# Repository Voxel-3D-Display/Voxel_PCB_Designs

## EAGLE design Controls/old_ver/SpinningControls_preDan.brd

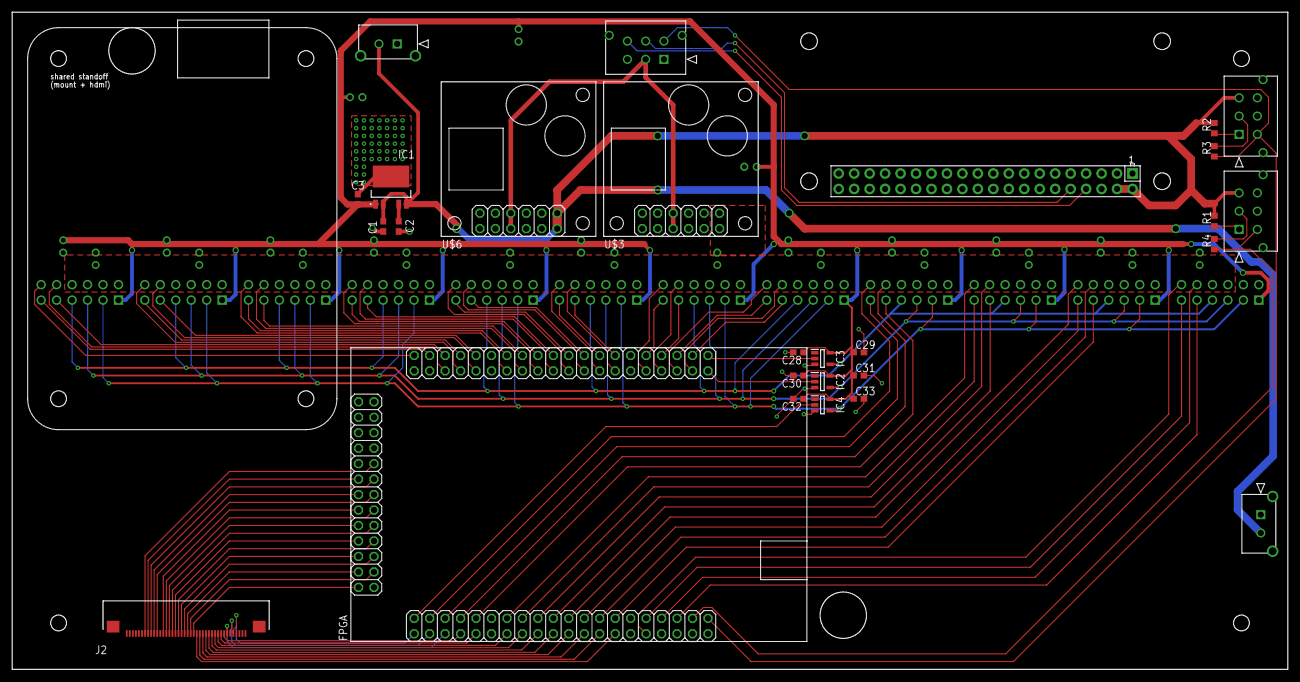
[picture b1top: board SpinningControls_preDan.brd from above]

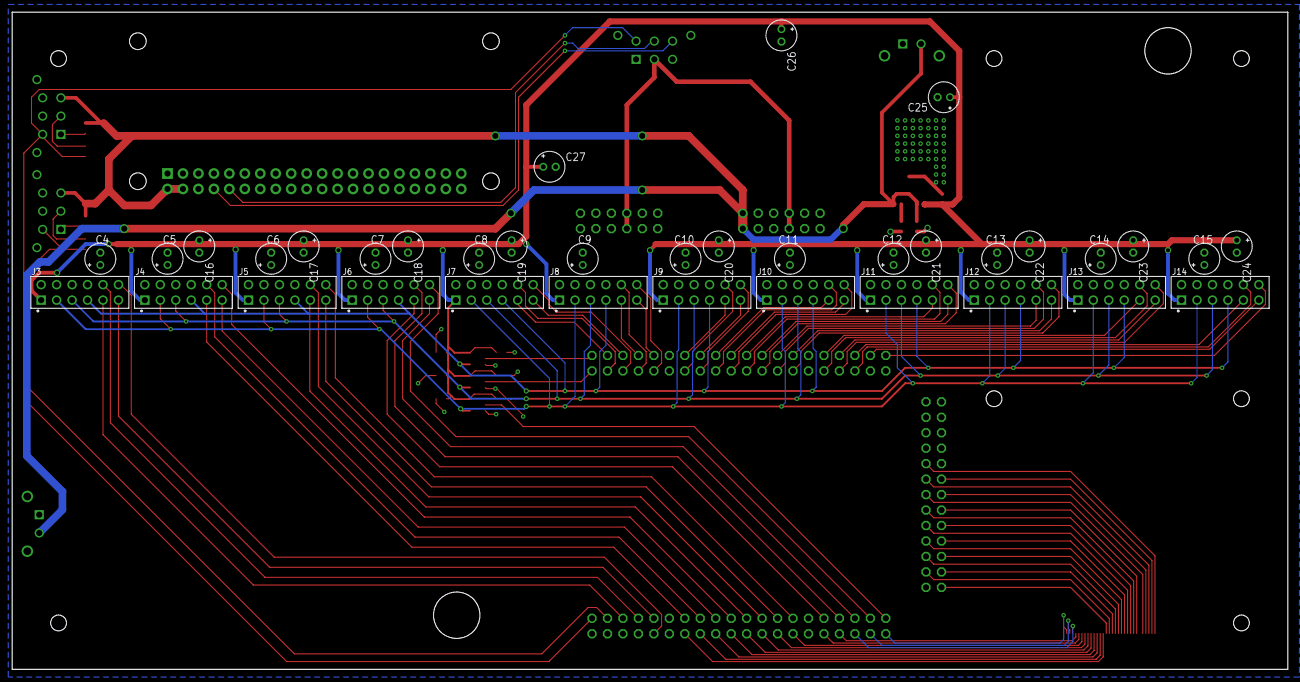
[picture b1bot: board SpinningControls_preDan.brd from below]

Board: 2 copper layers, 209.6 x 107.9 mm, 64 parts (36 on the bottom side), 95 nets.

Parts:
C1, C3: 4.7uF; C0603
C2: 10nF; C0603
C4, C5, C6, C7, C8, C9, C10, C11, C12, C13, C14, C15, C16, C17, C18, C19, C20, C21, C22, C23, C24, C25, C26, C27: 100u; E2-5
C28, C30, C32: 0.1u; C0603
C29, C31, C33: 4.7u; C0603
FPGA: DE0-NANO
IC1: S-19246E33H-V5T2U; S19246E33HV5T2U
IC2, IC3, IC4: SN74LVC1G34DBVR; SOT95P280X145-5N
J2: F32R-1A7H1-11040; F32R1A7H111040
J3, J4, J5, J6, J7, J8, J9, J10, J11, J12, J13, J14: SULLINS_PPPC062LFBN-RCSULLINS_PPPC062LFBN-RC_0_0; SULLINS_PPPC062LFBN-RC_0
J15, J16, J17: 430450612; CON_430450612_MOL
J18, J19: 436500215; CON_436500215_MOL
R1, R2: 165 Ω; R0603
R3, R4: 19.1k Ω; R0603
U$1: RPI-ZERO; RASPBERRYPI_BASTELSTUBE_V13_RASPI_BOARD_B+_FULL
U$2: TFP401
U$3: 3V3_BUCK_REGULATOR; 2X06
U$6: 5V_BUCK_REGULATOR; 2X06

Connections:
3V3_LED: C4.+, C5.+, C6.+, C7.+, C8.+, C9.+, C10.+, C11.+, C12.+, C13.+, C14.+, C15.+, J3.6, J3.8, J4.6, J4.8, J5.6, J5.8, J6.6, J6.8, J7.6, J7.8, J8.6, J8.8, J9.6, J9.8, J10.6, J10.8, J11.6, J11.8, J12.6, J12.8, J13.6, J13.8, J14.6, J14.8, U$3.11, U$3.12
3V3_LOGIC: C3.1, C16.+, C17.+, C18.+, C19.+, C20.+, C21.+, C22.+, C23.+, C24.+, C25.+, C26.+, C27.+, C28.1, C29.1, C30.1, C31.1, C32.1, C33.1, IC1.1, IC2.5, IC3.5, IC4.5, J3.1, J4.1, J5.1, J6.1, J7.1, J8.1, J9.1, J10.1, J11.1, J12.1, J13.1, J14.1
5V: C1.1, IC1.2, IC1.5, J16.3, J17.3, J18.2, J19.2, R1.2, R2.2, U$1.2, U$1.4, U$6.11, U$6.12
24V: J15.2, U$3.5, U$3.6, U$6.5, U$6.6
ACTIVE: FPGA.94, J2.31
B1: FPGA.85, J2.21
B2: FPGA.86, J2.22
B3: FPGA.87, J2.23
B4: FPGA.88, J2.24
B5: FPGA.89, J2.25
B6: FPGA.90, J2.26
B7: FPGA.91, J2.27
B8: FPGA.92, J2.28
DISPEN: FPGA.97, J2.34
ENC_POS: FPGA.41, J15.4, J17.4, R3.1
ENC_POS0: FPGA.43, J16.4, R4.1
G1: FPGA.62, J2.13
G2: FPGA.60, J2.14
G3: FPGA.58, J2.15
G4: FPGA.56, J2.16
G5: FPGA.54, J2.17
G6: FPGA.82, J2.18
G7: FPGA.83, J2.19
G8: FPGA.84, J2.20
GND: C1.2, C2.2, C3.2, C4.-, C5.-, C6.-, C7.-, C8.-, C9.-, C10.-, C11.-, C12.-, C13.-, C14.-, C15.-, C16.-, C17.-, C18.-, C19.-, C20.-, C21.-, C22.-, C23.-, C24.-, C25.-, C26.-, C27.-, C28.2, C29.2, C30.2, C31.2, C32.2, C33.2, IC1.3, IC2.3, IC3.3, IC4.3, J3.2, J3.4, J4.2, J4.4, J5.2, J5.4, J6.2, J6.4, J7.2, J7.4, J8.2, J8.4, J9.2, J9.4, J10.2, J10.4, J11.2, J11.4, J12.2, J12.4, J13.2, J13.4, J14.2, J14.4, J15.1, J15.3, J16.2, J16.5, J17.2, J17.5, J18.1, J19.1, R3.2, R4.2, U$1.6, U$1.9, U$1.14, U$1.20, U$1.25, U$1.30, U$1.34, U$1.39, U$3.7, U$3.8, U$3.9, U$3.10, U$6.7, U$6.8, U$6.9, U$6.10
GSCLK: IC4.4, J3.3, J4.3, J5.3, J6.3, J7.3, J8.3, J9.3, J10.3, J11.3, J12.3, J13.3, J14.3
GSCLK_FPGA: FPGA.79, IC4.2
HSYNC: FPGA.95, J2.32
LAT: IC2.4, J3.5, J4.5, J5.5, J6.5, J7.5, J8.5, J9.5, J10.5, J11.5, J12.5, J13.5, J14.5
LAT_FPGA: FPGA.39, IC2.2
unnamed: J16.1, R1.1
unnamed: C2.1, IC1.4
unnamed: J17.1, R2.1
PIXCLK: FPGA.93, J2.30
PI_RX: J15.5, U$1.10
PI_TX: J15.6, U$1.8
R1: FPGA.80, J2.5
R2: FPGA.78, J2.6
R3: FPGA.76, J2.7
R4: FPGA.74, J2.8
R5: FPGA.72, J2.9
R6: FPGA.68, J2.10
R7: FPGA.66, J2.11
R8: FPGA.64, J2.12
SCLK: IC3.4, J3.7, J4.7, J5.7, J6.7, J7.7, J8.7, J9.7, J10.7, J11.7, J12.7, J13.7, J14.7
SCLK_FPGA: FPGA.40, IC3.2
SIN12_J3: FPGA.50, J3.12
SIN12_J4: FPGA.59, J4.12
SIN12_J5: FPGA.67, J5.12
SIN12_J6: FPGA.77, J6.12
SIN12_J7: FPGA.35, J7.12
SIN12_J8: FPGA.31, J8.12
SIN12_J9: FPGA.25, J9.12
SIN12_J10: FPGA.21, J10.12
SIN12_J11: FPGA.17, J11.12
SIN12_J12: FPGA.13, J12.12
SIN12_J13: FPGA.7, J13.12
SIN12_J14: FPGA.2, J14.12
SIN34_J3: FPGA.49, J3.11
SIN34_J4: FPGA.57, J4.11
SIN34_J5: FPGA.65, J5.11
SIN34_J6: FPGA.75, J6.11
SIN34_J7: FPGA.36, J7.11
SIN34_J8: FPGA.32, J8.11
SIN34_J9: FPGA.26, J9.11
SIN34_J10: FPGA.22, J10.11
SIN34_J11: FPGA.18, J11.11
SIN34_J12: FPGA.14, J12.11
SIN34_J13: FPGA.8, J13.11
SIN34_J14: FPGA.4, J14.11
SIN56_J3: FPGA.47, J3.10
SIN56_J4: FPGA.55, J4.10
SIN56_J5: FPGA.63, J5.10
SIN56_J6: FPGA.73, J6.10
SIN56_J7: FPGA.37, J7.10
SIN56_J8: FPGA.33, J8.10
SIN56_J9: FPGA.27, J9.10
SIN56_J10: FPGA.23, J10.10
SIN56_J11: FPGA.19, J11.10
SIN56_J12: FPGA.15, J12.10
SIN56_J13: FPGA.9, J13.10
SIN56_J14: FPGA.5, J14.10
SIN78_J3: FPGA.45, J3.9
SIN78_J4: FPGA.53, J4.9
SIN78_J5: FPGA.61, J5.9
SIN78_J6: FPGA.71, J6.9
SIN78_J7: FPGA.38, J7.9
SIN78_J8: FPGA.34, J8.9
SIN78_J9: FPGA.28, J9.9
SIN78_J10: FPGA.24, J10.9
SIN78_J11: FPGA.20, J11.9
SIN78_J12: FPGA.16, J12.9
SIN78_J13: FPGA.10, J13.9
SIN78_J14: FPGA.6, J14.9
VSYNC: FPGA.96, J2.33

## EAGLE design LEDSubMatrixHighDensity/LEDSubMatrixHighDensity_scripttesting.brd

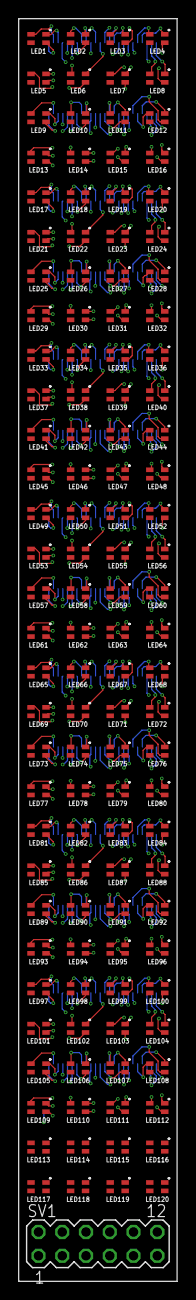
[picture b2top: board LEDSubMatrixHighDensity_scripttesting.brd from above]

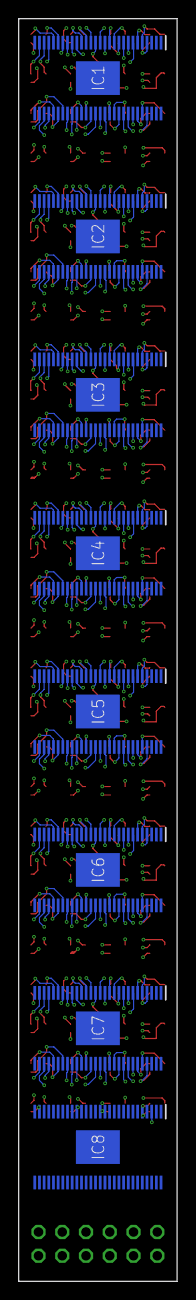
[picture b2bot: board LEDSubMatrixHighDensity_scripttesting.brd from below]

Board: 4 copper layers, 16.9 x 135.0 mm, 129 parts (8 on the bottom side), 369 nets.

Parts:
IC1, IC2, IC3, IC4, IC5, IC6, IC7, IC8: TLC5955DCAR; SOP50P810X120-57N
LED1, LED2, LED3, LED4, LED5, LED6, LED7, LED8, LED9, LED10, LED11, LED12, LED13, LED14, LED15, LED16, LED17, LED18, LED19, LED20, LED21, LED22, LED23, LED24, LED25, LED26, LED27, LED28, LED29, LED30, LED31, LED32, LED33, LED34, LED35, LED36, LED37, LED38, LED39, LED40, LED41, LED42, LED43, LED44, LED45, LED46, LED47, LED48, LED49, LED50, LED51, LED52, LED53, LED54, LED55, LED56, LED57, LED58, LED59, LED60, LED61, LED62, LED63, LED64, LED65, LED66, LED67, LED68, LED69, LED70, LED71, LED72, LED73, LED74, LED75, LED76, LED77, LED78, LED79, LED80, LED81, LED82, LED83, LED84, LED85, LED86, LED87, LED88, LED89, LED90, LED91, LED92, LED93, LED94, LED95, LED96, LED97, LED98, LED99, LED100, LED101, LED102, LED103, LED104, LED105, LED106, LED107, LED108, LED109, LED110, LED111, LED112, LED113, LED114, LED115, LED116, LED117, LED118, LED119, LED120: B38G3RGB
SV1: MA06-2

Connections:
3V3: IC1.54, IC2.54, IC3.54, IC4.54, IC5.54, IC6.54, IC7.54, IC8.54, LED1.3, LED2.3, LED3.3, LED4.3, LED5.3, LED6.3, LED7.3, LED8.3, LED9.3, LED10.3, LED11.3, LED12.3, LED13.3, LED14.3, LED15.3, LED16.3, LED17.3, LED18.3, LED19.3, LED20.3, LED21.3, LED22.3, LED23.3, LED24.3, LED25.3, LED26.3, LED27.3, LED28.3, LED29.3, LED30.3, LED31.3, LED32.3, LED33.3, LED34.3, LED35.3, LED36.3, LED37.3, LED38.3, LED39.3, LED40.3, LED41.3, LED42.3, LED43.3, LED44.3, LED45.3, LED46.3, LED47.3, LED48.3, LED49.3, LED50.3, LED51.3, LED52.3, LED53.3, LED54.3, LED55.3, LED56.3, LED57.3, LED58.3, LED59.3, LED60.3, LED61.3, LED62.3, LED63.3, LED64.3, LED65.3, LED66.3, LED67.3, LED68.3, LED69.3, LED70.3, LED71.3, LED72.3, LED73.3, LED74.3, LED75.3, LED76.3, LED77.3, LED78.3, LED79.3, LED80.3, LED81.3, LED82.3, LED83.3, LED84.3, LED85.3, LED86.3, LED87.3, LED88.3, LED89.3, LED90.3, LED91.3, LED92.3, LED93.3, LED94.3, LED95.3, LED96.3, LED97.3, LED98.3, LED99.3, LED100.3, LED101.3, LED102.3, LED103.3, LED104.3, LED105.3, LED106.3, LED107.3, LED108.3, LED109.3, LED110.3, LED111.3, LED112.3, LED113.3, LED114.3, LED115.3, LED116.3, LED117.3, LED118.3, LED119.3, LED120.3, SV1.3, SV1.9, SV1.10
GND: IC1.29, IC1.56, IC1.57, IC2.29, IC2.56, IC2.57, IC3.29, IC3.56, IC3.57, IC4.29, IC4.56, IC4.57, IC5.29, IC5.56, IC5.57, IC6.29, IC6.56, IC6.57, IC7.29, IC7.56, IC7.57, IC8.29, IC8.56, IC8.57, SV1.1, SV1.11, SV1.12
GSCLK: IC1.55, IC2.55, IC3.55, IC4.55, IC5.55, IC6.55, IC7.55, IC8.55, SV1.6
LAT: IC1.3, IC2.3, IC3.3, IC4.3, IC5.3, IC6.3, IC7.3, IC8.3, SV1.4, SV1.8
N$LEDB1_IC1_PIN4: IC1.4, LED1.2
N$LEDB2_IC1_PIN10: IC1.10, LED2.2
N$LEDB3_IC1_PIN16: IC1.16, LED3.2
N$LEDB4_IC1_PIN22: IC1.22, LED4.2
N$LEDB5_IC1_PIN7: IC1.7, LED5.2
N$LEDB6_IC1_PIN13: IC1.13, LED6.2
N$LEDB7_IC1_PIN19: IC1.19, LED7.2
N$LEDB8_IC1_PIN25: IC1.25, LED8.2
N$LEDB9_IC1_PIN53: IC1.53, LED9.2
N$LEDB10_IC1_PIN47: IC1.47, LED10.2
N$LEDB11_IC1_PIN41: IC1.41, LED11.2
N$LEDB12_IC1_PIN35: IC1.35, LED12.2
N$LEDB13_IC1_PIN50: IC1.50, LED13.2
N$LEDB14_IC1_PIN44: IC1.44, LED14.2
N$LEDB15_IC1_PIN38: IC1.38, LED15.2
N$LEDB16_IC1_PIN32: IC1.32, LED16.2
N$LEDB17_IC2_PIN4: IC2.4, LED17.2
N$LEDB18_IC2_PIN10: IC2.10, LED18.2
N$LEDB19_IC2_PIN16: IC2.16, LED19.2
N$LEDB20_IC2_PIN22: IC2.22, LED20.2
N$LEDB21_IC2_PIN7: IC2.7, LED21.2
N$LEDB22_IC2_PIN13: IC2.13, LED22.2
N$LEDB23_IC2_PIN19: IC2.19, LED23.2
N$LEDB24_IC2_PIN25: IC2.25, LED24.2
N$LEDB25_IC2_PIN53: IC2.53, LED25.2
N$LEDB26_IC2_PIN47: IC2.47, LED26.2
N$LEDB27_IC2_PIN41: IC2.41, LED27.2
N$LEDB28_IC2_PIN35: IC2.35, LED28.2
N$LEDB29_IC2_PIN50: IC2.50, LED29.2
N$LEDB30_IC2_PIN44: IC2.44, LED30.2
N$LEDB31_IC2_PIN38: IC2.38, LED31.2
N$LEDB32_IC2_PIN32: IC2.32, LED32.2
N$LEDB33_IC3_PIN4: IC3.4, LED33.2
N$LEDB34_IC3_PIN10: IC3.10, LED34.2
N$LEDB35_IC3_PIN16: IC3.16, LED35.2
N$LEDB36_IC3_PIN22: IC3.22, LED36.2
N$LEDB37_IC3_PIN7: IC3.7, LED37.2
N$LEDB38_IC3_PIN13: IC3.13, LED38.2
N$LEDB39_IC3_PIN19: IC3.19, LED39.2
N$LEDB40_IC3_PIN25: IC3.25, LED40.2
N$LEDB41_IC3_PIN53: IC3.53, LED41.2
N$LEDB42_IC3_PIN47: IC3.47, LED42.2
N$LEDB43_IC3_PIN41: IC3.41, LED43.2
N$LEDB44_IC3_PIN35: IC3.35, LED44.2
N$LEDB45_IC3_PIN50: IC3.50, LED45.2
N$LEDB46_IC3_PIN44: IC3.44, LED46.2
N$LEDB47_IC3_PIN38: IC3.38, LED47.2
N$LEDB48_IC3_PIN32: IC3.32, LED48.2
N$LEDB49_IC4_PIN4: IC4.4, LED49.2
N$LEDB50_IC4_PIN10: IC4.10, LED50.2
N$LEDB51_IC4_PIN16: IC4.16, LED51.2
N$LEDB52_IC4_PIN22: IC4.22, LED52.2
N$LEDB53_IC4_PIN7: IC4.7, LED53.2
N$LEDB54_IC4_PIN13: IC4.13, LED54.2
N$LEDB55_IC4_PIN19: IC4.19, LED55.2
N$LEDB56_IC4_PIN25: IC4.25, LED56.2
N$LEDB57_IC4_PIN53: IC4.53, LED57.2
N$LEDB58_IC4_PIN47: IC4.47, LED58.2
N$LEDB59_IC4_PIN41: IC4.41, LED59.2
N$LEDB60_IC4_PIN35: IC4.35, LED60.2
N$LEDB61_IC4_PIN50: IC4.50, LED61.2
N$LEDB62_IC4_PIN44: IC4.44, LED62.2
N$LEDB63_IC4_PIN38: IC4.38, LED63.2
N$LEDB64_IC4_PIN32: IC4.32, LED64.2
N$LEDB65_IC5_PIN4: IC5.4, LED65.2
N$LEDB66_IC5_PIN10: IC5.10, LED66.2
N$LEDB67_IC5_PIN16: IC5.16, LED67.2
N$LEDB68_IC5_PIN22: IC5.22, LED68.2
N$LEDB69_IC5_PIN7: IC5.7, LED69.2
N$LEDB70_IC5_PIN13: IC5.13, LED70.2
N$LEDB71_IC5_PIN19: IC5.19, LED71.2
N$LEDB72_IC5_PIN25: IC5.25, LED72.2
N$LEDB73_IC5_PIN53: IC5.53, LED73.2
N$LEDB74_IC5_PIN47: IC5.47, LED74.2
N$LEDB75_IC5_PIN41: IC5.41, LED75.2
N$LEDB76_IC5_PIN35: IC5.35, LED76.2
N$LEDB77_IC5_PIN50: IC5.50, LED77.2
N$LEDB78_IC5_PIN44: IC5.44, LED78.2
N$LEDB79_IC5_PIN38: IC5.38, LED79.2
N$LEDB80_IC5_PIN32: IC5.32, LED80.2
N$LEDB81_IC6_PIN4: IC6.4, LED81.2
N$LEDB82_IC6_PIN10: IC6.10, LED82.2
N$LEDB83_IC6_PIN16: IC6.16, LED83.2
N$LEDB84_IC6_PIN22: IC6.22, LED84.2
N$LEDB85_IC6_PIN7: IC6.7, LED85.2
N$LEDB86_IC6_PIN13: IC6.13, LED86.2
N$LEDB87_IC6_PIN19: IC6.19, LED87.2
N$LEDB88_IC6_PIN25: IC6.25, LED88.2
N$LEDB89_IC6_PIN53: IC6.53, LED89.2
N$LEDB90_IC6_PIN47: IC6.47, LED90.2
N$LEDB91_IC6_PIN41: IC6.41, LED91.2
N$LEDB92_IC6_PIN35: IC6.35, LED92.2
N$LEDB93_IC6_PIN50: IC6.50, LED93.2
N$LEDB94_IC6_PIN44: IC6.44, LED94.2
N$LEDB95_IC6_PIN38: IC6.38, LED95.2
N$LEDB96_IC6_PIN32: IC6.32, LED96.2
N$LEDB97_IC7_PIN4: IC7.4, LED97.2
N$LEDB98_IC7_PIN10: IC7.10, LED98.2
N$LEDB99_IC7_PIN16: IC7.16, LED99.2
N$LEDB100_IC7_PIN22: IC7.22, LED100.2
N$LEDB101_IC7_PIN7: IC7.7, LED101.2
N$LEDB102_IC7_PIN13: IC7.13, LED102.2
N$LEDB103_IC7_PIN19: IC7.19, LED103.2
N$LEDB104_IC7_PIN25: IC7.25, LED104.2
N$LEDB105_IC7_PIN53: IC7.53, LED105.2
N$LEDB106_IC7_PIN47: IC7.47, LED106.2
N$LEDB107_IC7_PIN41: IC7.41, LED107.2
N$LEDB108_IC7_PIN35: IC7.35, LED108.2
N$LEDB109_IC7_PIN50: IC7.50, LED109.2
N$LEDB110_IC7_PIN44: IC7.44, LED110.2
N$LEDB111_IC7_PIN38: IC7.38, LED111.2
N$LEDB112_IC7_PIN32: IC7.32, LED112.2
N$LEDB113_IC8_PIN4: IC8.4, LED113.2
N$LEDB114_IC8_PIN10: IC8.10, LED114.2
N$LEDB115_IC8_PIN16: IC8.16, LED115.2
N$LEDB116_IC8_PIN22: IC8.22, LED116.2
N$LEDB117_IC8_PIN7: IC8.7, LED117.2
N$LEDB118_IC8_PIN13: IC8.13, LED118.2
N$LEDB119_IC8_PIN19: IC8.19, LED119.2
N$LEDB120_IC8_PIN25: IC8.25, LED120.2
N$LEDG1_IC1_PIN6: IC1.6, LED1.1
N$LEDG2_IC1_PIN12: IC1.12, LED2.1
N$LEDG3_IC1_PIN18: IC1.18, LED3.1
N$LEDG4_IC1_PIN24: IC1.24, LED4.1
N$LEDG5_IC1_PIN9: IC1.9, LED5.1
N$LEDG6_IC1_PIN15: IC1.15, LED6.1
N$LEDG7_IC1_PIN21: IC1.21, LED7.1
N$LEDG8_IC1_PIN27: IC1.27, LED8.1
N$LEDG9_IC1_PIN51: IC1.51, LED9.1
N$LEDG10_IC1_PIN45: IC1.45, LED10.1
N$LEDG11_IC1_PIN39: IC1.39, LED11.1
N$LEDG12_IC1_PIN33: IC1.33, LED12.1
N$LEDG13_IC1_PIN48: IC1.48, LED13.1
N$LEDG14_IC1_PIN42: IC1.42, LED14.1
N$LEDG15_IC1_PIN36: IC1.36, LED15.1
N$LEDG16_IC1_PIN30: IC1.30, LED16.1
N$LEDG17_IC2_PIN6: IC2.6, LED17.1
N$LEDG18_IC2_PIN12: IC2.12, LED18.1
N$LEDG19_IC2_PIN18: IC2.18, LED19.1
N$LEDG20_IC2_PIN24: IC2.24, LED20.1
N$LEDG21_IC2_PIN9: IC2.9, LED21.1
N$LEDG22_IC2_PIN15: IC2.15, LED22.1
N$LEDG23_IC2_PIN21: IC2.21, LED23.1
N$LEDG24_IC2_PIN27: IC2.27, LED24.1
N$LEDG25_IC2_PIN51: IC2.51, LED25.1
N$LEDG26_IC2_PIN45: IC2.45, LED26.1
N$LEDG27_IC2_PIN39: IC2.39, LED27.1
N$LEDG28_IC2_PIN33: IC2.33, LED28.1
N$LEDG29_IC2_PIN48: IC2.48, LED29.1
N$LEDG30_IC2_PIN42: IC2.42, LED30.1
N$LEDG31_IC2_PIN36: IC2.36, LED31.1
N$LEDG32_IC2_PIN30: IC2.30, LED32.1
N$LEDG33_IC3_PIN6: IC3.6, LED33.1
N$LEDG34_IC3_PIN12: IC3.12, LED34.1
N$LEDG35_IC3_PIN18: IC3.18, LED35.1
N$LEDG36_IC3_PIN24: IC3.24, LED36.1
N$LEDG37_IC3_PIN9: IC3.9, LED37.1
N$LEDG38_IC3_PIN15: IC3.15, LED38.1
N$LEDG39_IC3_PIN21: IC3.21, LED39.1
N$LEDG40_IC3_PIN27: IC3.27, LED40.1
N$LEDG41_IC3_PIN51: IC3.51, LED41.1
N$LEDG42_IC3_PIN45: IC3.45, LED42.1
N$LEDG43_IC3_PIN39: IC3.39, LED43.1
N$LEDG44_IC3_PIN33: IC3.33, LED44.1
N$LEDG45_IC3_PIN48: IC3.48, LED45.1
N$LEDG46_IC3_PIN42: IC3.42, LED46.1
N$LEDG47_IC3_PIN36: IC3.36, LED47.1
N$LEDG48_IC3_PIN30: IC3.30, LED48.1
N$LEDG49_IC4_PIN6: IC4.6, LED49.1
N$LEDG50_IC4_PIN12: IC4.12, LED50.1
N$LEDG51_IC4_PIN18: IC4.18, LED51.1
N$LEDG52_IC4_PIN24: IC4.24, LED52.1
N$LEDG53_IC4_PIN9: IC4.9, LED53.1
N$LEDG54_IC4_PIN15: IC4.15, LED54.1
N$LEDG55_IC4_PIN21: IC4.21, LED55.1
N$LEDG56_IC4_PIN27: IC4.27, LED56.1
N$LEDG57_IC4_PIN51: IC4.51, LED57.1
N$LEDG58_IC4_PIN45: IC4.45, LED58.1
N$LEDG59_IC4_PIN39: IC4.39, LED59.1
N$LEDG60_IC4_PIN33: IC4.33, LED60.1
N$LEDG61_IC4_PIN48: IC4.48, LED61.1
N$LEDG62_IC4_PIN42: IC4.42, LED62.1
N$LEDG63_IC4_PIN36: IC4.36, LED63.1
N$LEDG64_IC4_PIN30: IC4.30, LED64.1
N$LEDG65_IC5_PIN6: IC5.6, LED65.1
N$LEDG66_IC5_PIN12: IC5.12, LED66.1
N$LEDG67_IC5_PIN18: IC5.18, LED67.1
N$LEDG68_IC5_PIN24: IC5.24, LED68.1
N$LEDG69_IC5_PIN9: IC5.9, LED69.1
N$LEDG70_IC5_PIN15: IC5.15, LED70.1
N$LEDG71_IC5_PIN21: IC5.21, LED71.1
N$LEDG72_IC5_PIN27: IC5.27, LED72.1
N$LEDG73_IC5_PIN51: IC5.51, LED73.1
N$LEDG74_IC5_PIN45: IC5.45, LED74.1
N$LEDG75_IC5_PIN39: IC5.39, LED75.1
N$LEDG76_IC5_PIN33: IC5.33, LED76.1
N$LEDG77_IC5_PIN48: IC5.48, LED77.1
N$LEDG78_IC5_PIN42: IC5.42, LED78.1
N$LEDG79_IC5_PIN36: IC5.36, LED79.1
N$LEDG80_IC5_PIN30: IC5.30, LED80.1
N$LEDG81_IC6_PIN6: IC6.6, LED81.1
N$LEDG82_IC6_PIN12: IC6.12, LED82.1
N$LEDG83_IC6_PIN18: IC6.18, LED83.1
N$LEDG84_IC6_PIN24: IC6.24, LED84.1
N$LEDG85_IC6_PIN9: IC6.9, LED85.1
N$LEDG86_IC6_PIN15: IC6.15, LED86.1
N$LEDG87_IC6_PIN21: IC6.21, LED87.1
N$LEDG88_IC6_PIN27: IC6.27, LED88.1
N$LEDG89_IC6_PIN51: IC6.51, LED89.1
N$LEDG90_IC6_PIN45: IC6.45, LED90.1
N$LEDG91_IC6_PIN39: IC6.39, LED91.1
N$LEDG92_IC6_PIN33: IC6.33, LED92.1
N$LEDG93_IC6_PIN48: IC6.48, LED93.1
N$LEDG94_IC6_PIN42: IC6.42, LED94.1
N$LEDG95_IC6_PIN36: IC6.36, LED95.1
N$LEDG96_IC6_PIN30: IC6.30, LED96.1
N$LEDG97_IC7_PIN6: IC7.6, LED97.1
N$LEDG98_IC7_PIN12: IC7.12, LED98.1
N$LEDG99_IC7_PIN18: IC7.18, LED99.1
N$LEDG100_IC7_PIN24: IC7.24, LED100.1
N$LEDG101_IC7_PIN9: IC7.9, LED101.1
N$LEDG102_IC7_PIN15: IC7.15, LED102.1
N$LEDG103_IC7_PIN21: IC7.21, LED103.1
N$LEDG104_IC7_PIN27: IC7.27, LED104.1
N$LEDG105_IC7_PIN51: IC7.51, LED105.1
N$LEDG106_IC7_PIN45: IC7.45, LED106.1
N$LEDG107_IC7_PIN39: IC7.39, LED107.1
N$LEDG108_IC7_PIN33: IC7.33, LED108.1
N$LEDG109_IC7_PIN48: IC7.48, LED109.1
N$LEDG110_IC7_PIN42: IC7.42, LED110.1
N$LEDG111_IC7_PIN36: IC7.36, LED111.1
N$LEDG112_IC7_PIN30: IC7.30, LED112.1
N$LEDG113_IC8_PIN6: IC8.6, LED113.1
N$LEDG114_IC8_PIN12: IC8.12, LED114.1
N$LEDG115_IC8_PIN18: IC8.18, LED115.1
N$LEDG116_IC8_PIN24: IC8.24, LED116.1
N$LEDG117_IC8_PIN9: IC8.9, LED117.1
N$LEDG118_IC8_PIN15: IC8.15, LED118.1
N$LEDG119_IC8_PIN21: IC8.21, LED119.1
N$LEDG120_IC8_PIN27: IC8.27, LED120.1
N$LEDR1_IC1_PIN5: IC1.5, LED1.4
N$LEDR2_IC1_PIN11: IC1.11, LED2.4
N$LEDR3_IC1_PIN17: IC1.17, LED3.4
N$LEDR4_IC1_PIN23: IC1.23, LED4.4
N$LEDR5_IC1_PIN8: IC1.8, LED5.4
N$LEDR6_IC1_PIN14: IC1.14, LED6.4
N$LEDR7_IC1_PIN20: IC1.20, LED7.4
N$LEDR8_IC1_PIN26: IC1.26, LED8.4
N$LEDR9_IC1_PIN52: IC1.52, LED9.4
N$LEDR10_IC1_PIN46: IC1.46, LED10.4
N$LEDR11_IC1_PIN40: IC1.40, LED11.4
N$LEDR12_IC1_PIN34: IC1.34, LED12.4
N$LEDR13_IC1_PIN49: IC1.49, LED13.4
N$LEDR14_IC1_PIN43: IC1.43, LED14.4
N$LEDR15_IC1_PIN37: IC1.37, LED15.4
N$LEDR16_IC1_PIN31: IC1.31, LED16.4
N$LEDR17_IC2_PIN5: IC2.5, LED17.4
N$LEDR18_IC2_PIN11: IC2.11, LED18.4
N$LEDR19_IC2_PIN17: IC2.17, LED19.4
N$LEDR20_IC2_PIN23: IC2.23, LED20.4
N$LEDR21_IC2_PIN8: IC2.8, LED21.4
N$LEDR22_IC2_PIN14: IC2.14, LED22.4
N$LEDR23_IC2_PIN20: IC2.20, LED23.4
N$LEDR24_IC2_PIN26: IC2.26, LED24.4
N$LEDR25_IC2_PIN52: IC2.52, LED25.4
N$LEDR26_IC2_PIN46: IC2.46, LED26.4
N$LEDR27_IC2_PIN40: IC2.40, LED27.4
N$LEDR28_IC2_PIN34: IC2.34, LED28.4
N$LEDR29_IC2_PIN49: IC2.49, LED29.4
N$LEDR30_IC2_PIN43: IC2.43, LED30.4
N$LEDR31_IC2_PIN37: IC2.37, LED31.4
N$LEDR32_IC2_PIN31: IC2.31, LED32.4
N$LEDR33_IC3_PIN5: IC3.5, LED33.4
N$LEDR34_IC3_PIN11: IC3.11, LED34.4
N$LEDR35_IC3_PIN17: IC3.17, LED35.4
N$LEDR36_IC3_PIN23: IC3.23, LED36.4
N$LEDR37_IC3_PIN8: IC3.8, LED37.4
N$LEDR38_IC3_PIN14: IC3.14, LED38.4
N$LEDR39_IC3_PIN20: IC3.20, LED39.4
N$LEDR40_IC3_PIN26: IC3.26, LED40.4
N$LEDR41_IC3_PIN52: IC3.52, LED41.4
N$LEDR42_IC3_PIN46: IC3.46, LED42.4
N$LEDR43_IC3_PIN40: IC3.40, LED43.4
N$LEDR44_IC3_PIN34: IC3.34, LED44.4
N$LEDR45_IC3_PIN49: IC3.49, LED45.4
N$LEDR46_IC3_PIN43: IC3.43, LED46.4
N$LEDR47_IC3_PIN37: IC3.37, LED47.4
N$LEDR48_IC3_PIN31: IC3.31, LED48.4
N$LEDR49_IC4_PIN5: IC4.5, LED49.4
N$LEDR50_IC4_PIN11: IC4.11, LED50.4
N$LEDR51_IC4_PIN17: IC4.17, LED51.4
N$LEDR52_IC4_PIN23: IC4.23, LED52.4
N$LEDR53_IC4_PIN8: IC4.8, LED53.4
N$LEDR54_IC4_PIN14: IC4.14, LED54.4
N$LEDR55_IC4_PIN20: IC4.20, LED55.4
N$LEDR56_IC4_PIN26: IC4.26, LED56.4
N$LEDR57_IC4_PIN52: IC4.52, LED57.4
N$LEDR58_IC4_PIN46: IC4.46, LED58.4
N$LEDR59_IC4_PIN40: IC4.40, LED59.4
N$LEDR60_IC4_PIN34: IC4.34, LED60.4
N$LEDR61_IC4_PIN49: IC4.49, LED61.4
N$LEDR62_IC4_PIN43: IC4.43, LED62.4
N$LEDR63_IC4_PIN37: IC4.37, LED63.4
N$LEDR64_IC4_PIN31: IC4.31, LED64.4
N$LEDR65_IC5_PIN5: IC5.5, LED65.4
N$LEDR66_IC5_PIN11: IC5.11, LED66.4
N$LEDR67_IC5_PIN17: IC5.17, LED67.4
N$LEDR68_IC5_PIN23: IC5.23, LED68.4
N$LEDR69_IC5_PIN8: IC5.8, LED69.4
N$LEDR70_IC5_PIN14: IC5.14, LED70.4
N$LEDR71_IC5_PIN20: IC5.20, LED71.4
N$LEDR72_IC5_PIN26: IC5.26, LED72.4
N$LEDR73_IC5_PIN52: IC5.52, LED73.4
N$LEDR74_IC5_PIN46: IC5.46, LED74.4
N$LEDR75_IC5_PIN40: IC5.40, LED75.4
N$LEDR76_IC5_PIN34: IC5.34, LED76.4
N$LEDR77_IC5_PIN49: IC5.49, LED77.4
N$LEDR78_IC5_PIN43: IC5.43, LED78.4
N$LEDR79_IC5_PIN37: IC5.37, LED79.4
N$LEDR80_IC5_PIN31: IC5.31, LED80.4
N$LEDR81_IC6_PIN5: IC6.5, LED81.4
N$LEDR82_IC6_PIN11: IC6.11, LED82.4
N$LEDR83_IC6_PIN17: IC6.17, LED83.4
N$LEDR84_IC6_PIN23: IC6.23, LED84.4
N$LEDR85_IC6_PIN8: IC6.8, LED85.4
N$LEDR86_IC6_PIN14: IC6.14, LED86.4
N$LEDR87_IC6_PIN20: IC6.20, LED87.4
N$LEDR88_IC6_PIN26: IC6.26, LED88.4
N$LEDR89_IC6_PIN52: IC6.52, LED89.4
N$LEDR90_IC6_PIN46: IC6.46, LED90.4
N$LEDR91_IC6_PIN40: IC6.40, LED91.4
N$LEDR92_IC6_PIN34: IC6.34, LED92.4
N$LEDR93_IC6_PIN49: IC6.49, LED93.4
N$LEDR94_IC6_PIN43: IC6.43, LED94.4
N$LEDR95_IC6_PIN37: IC6.37, LED95.4
N$LEDR96_IC6_PIN31: IC6.31, LED96.4
N$LEDR97_IC7_PIN5: IC7.5, LED97.4
N$LEDR98_IC7_PIN11: IC7.11, LED98.4
N$LEDR99_IC7_PIN17: IC7.17, LED99.4
N$LEDR100_IC7_PIN23: IC7.23, LED100.4
N$LEDR101_IC7_PIN8: IC7.8, LED101.4
N$LEDR102_IC7_PIN14: IC7.14, LED102.4
N$LEDR103_IC7_PIN20: IC7.20, LED103.4
N$LEDR104_IC7_PIN26: IC7.26, LED104.4
N$LEDR105_IC7_PIN52: IC7.52, LED105.4
N$LEDR106_IC7_PIN46: IC7.46, LED106.4
N$LEDR107_IC7_PIN40: IC7.40, LED107.4
N$LEDR108_IC7_PIN34: IC7.34, LED108.4
N$LEDR109_IC7_PIN49: IC7.49, LED109.4
N$LEDR110_IC7_PIN43: IC7.43, LED110.4
N$LEDR111_IC7_PIN37: IC7.37, LED111.4
N$LEDR112_IC7_PIN31: IC7.31, LED112.4
N$LEDR113_IC8_PIN5: IC8.5, LED113.4
N$LEDR114_IC8_PIN11: IC8.11, LED114.4
N$LEDR115_IC8_PIN17: IC8.17, LED115.4
N$LEDR116_IC8_PIN23: IC8.23, LED116.4
N$LEDR117_IC8_PIN8: IC8.8, LED117.4
N$LEDR118_IC8_PIN14: IC8.14, LED118.4
N$LEDR119_IC8_PIN20: IC8.20, LED119.4
N$LEDR120_IC8_PIN26: IC8.26, LED120.4
SCLK: IC1.2, IC2.2, IC3.2, IC4.2, IC5.2, IC6.2, IC7.2, IC8.2, SV1.2, SV1.7
SIN_1,2: IC1.1, IC2.1
SIN_3,4: IC3.1, IC4.1
SIN_5,6: IC5.1, IC6.1
SIN_7,8: IC7.1, IC8.1

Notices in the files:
parts and their libraries:
COPYRIGHT: Copyright (C) 2022 Ultra Librarian. All rights reserved.
